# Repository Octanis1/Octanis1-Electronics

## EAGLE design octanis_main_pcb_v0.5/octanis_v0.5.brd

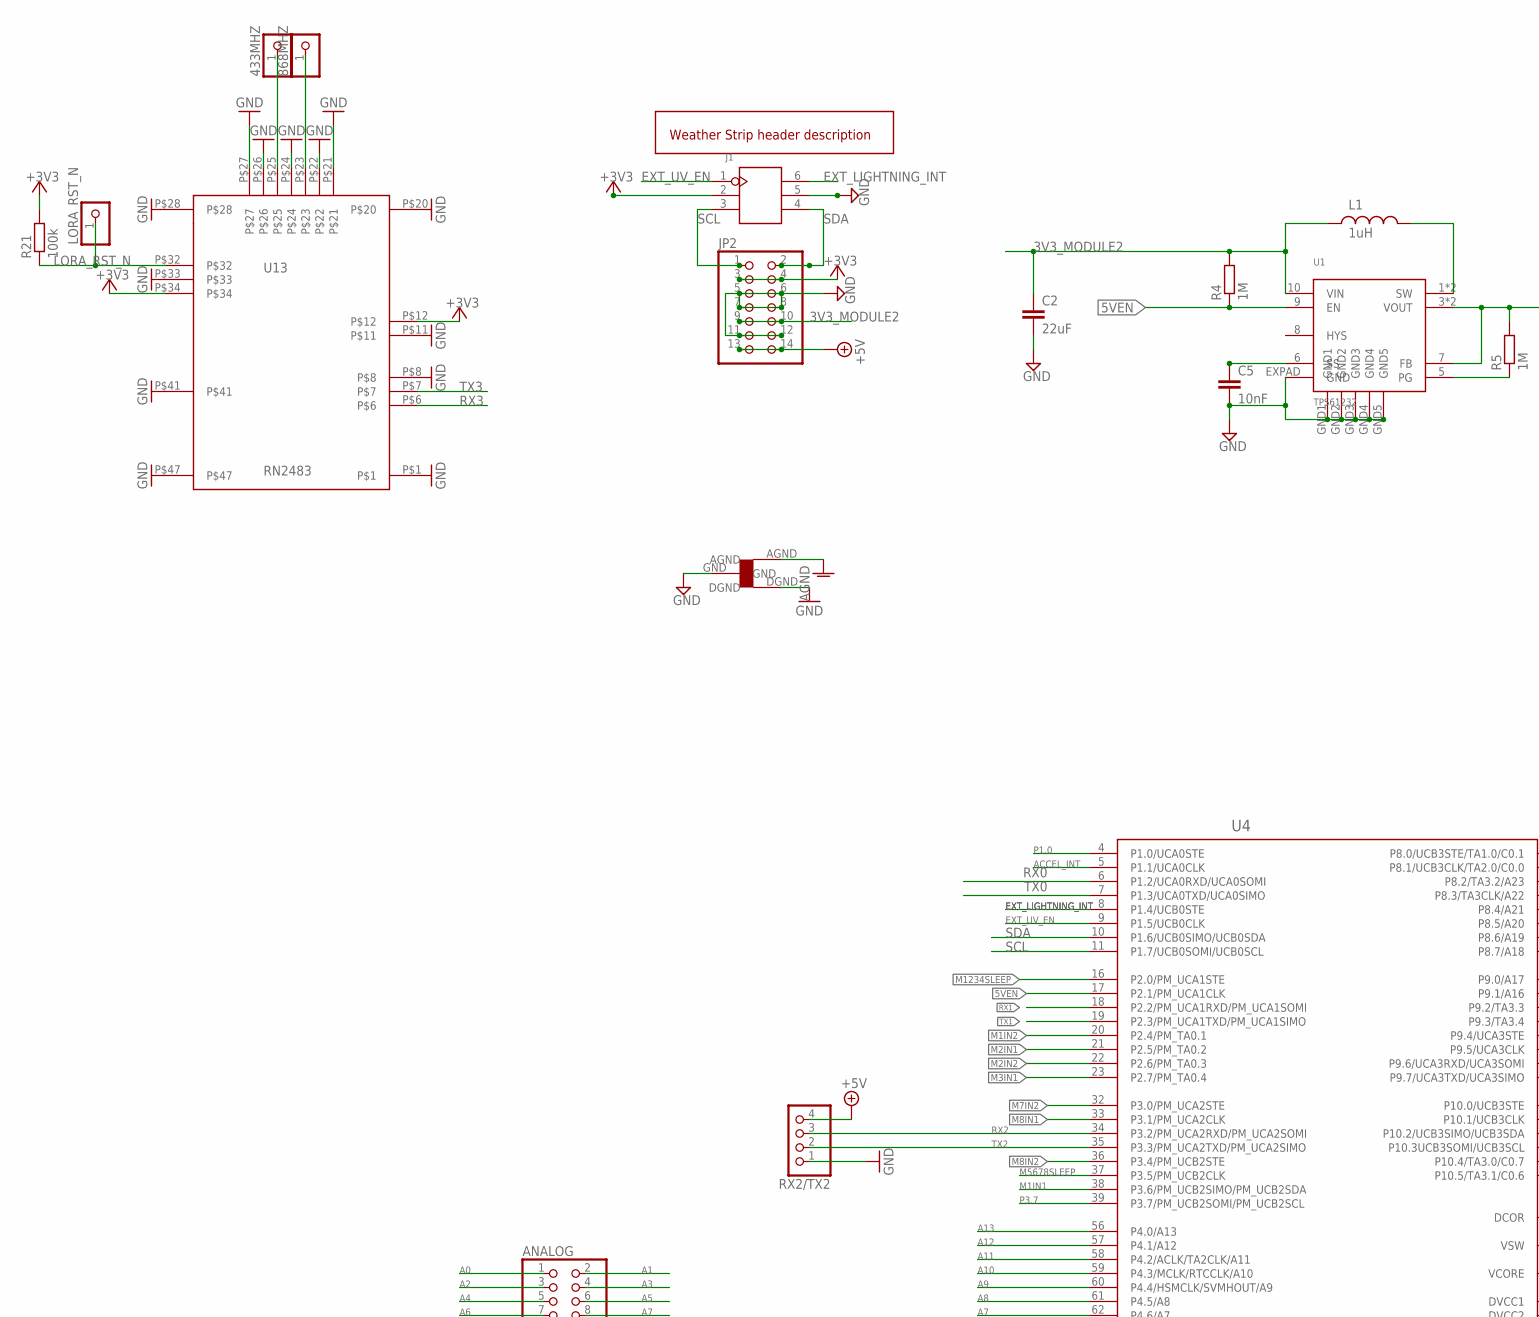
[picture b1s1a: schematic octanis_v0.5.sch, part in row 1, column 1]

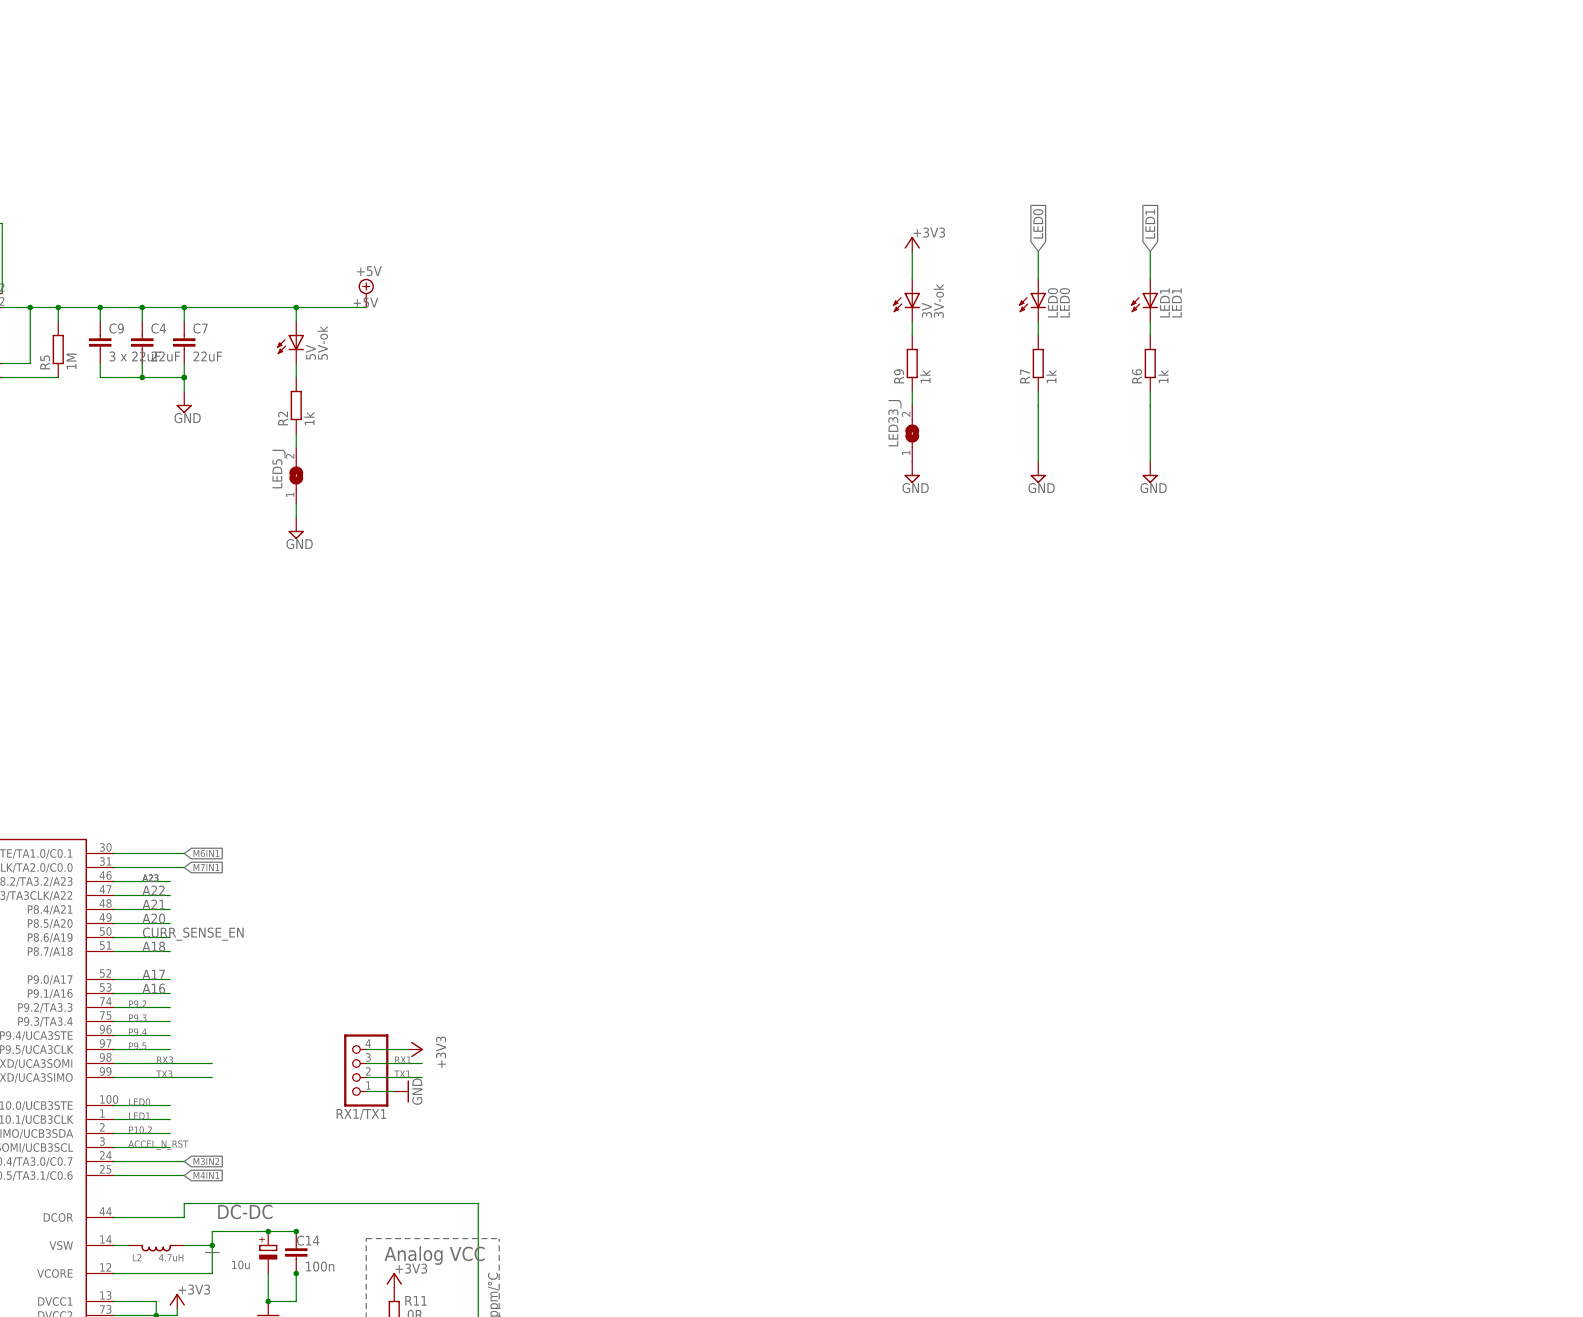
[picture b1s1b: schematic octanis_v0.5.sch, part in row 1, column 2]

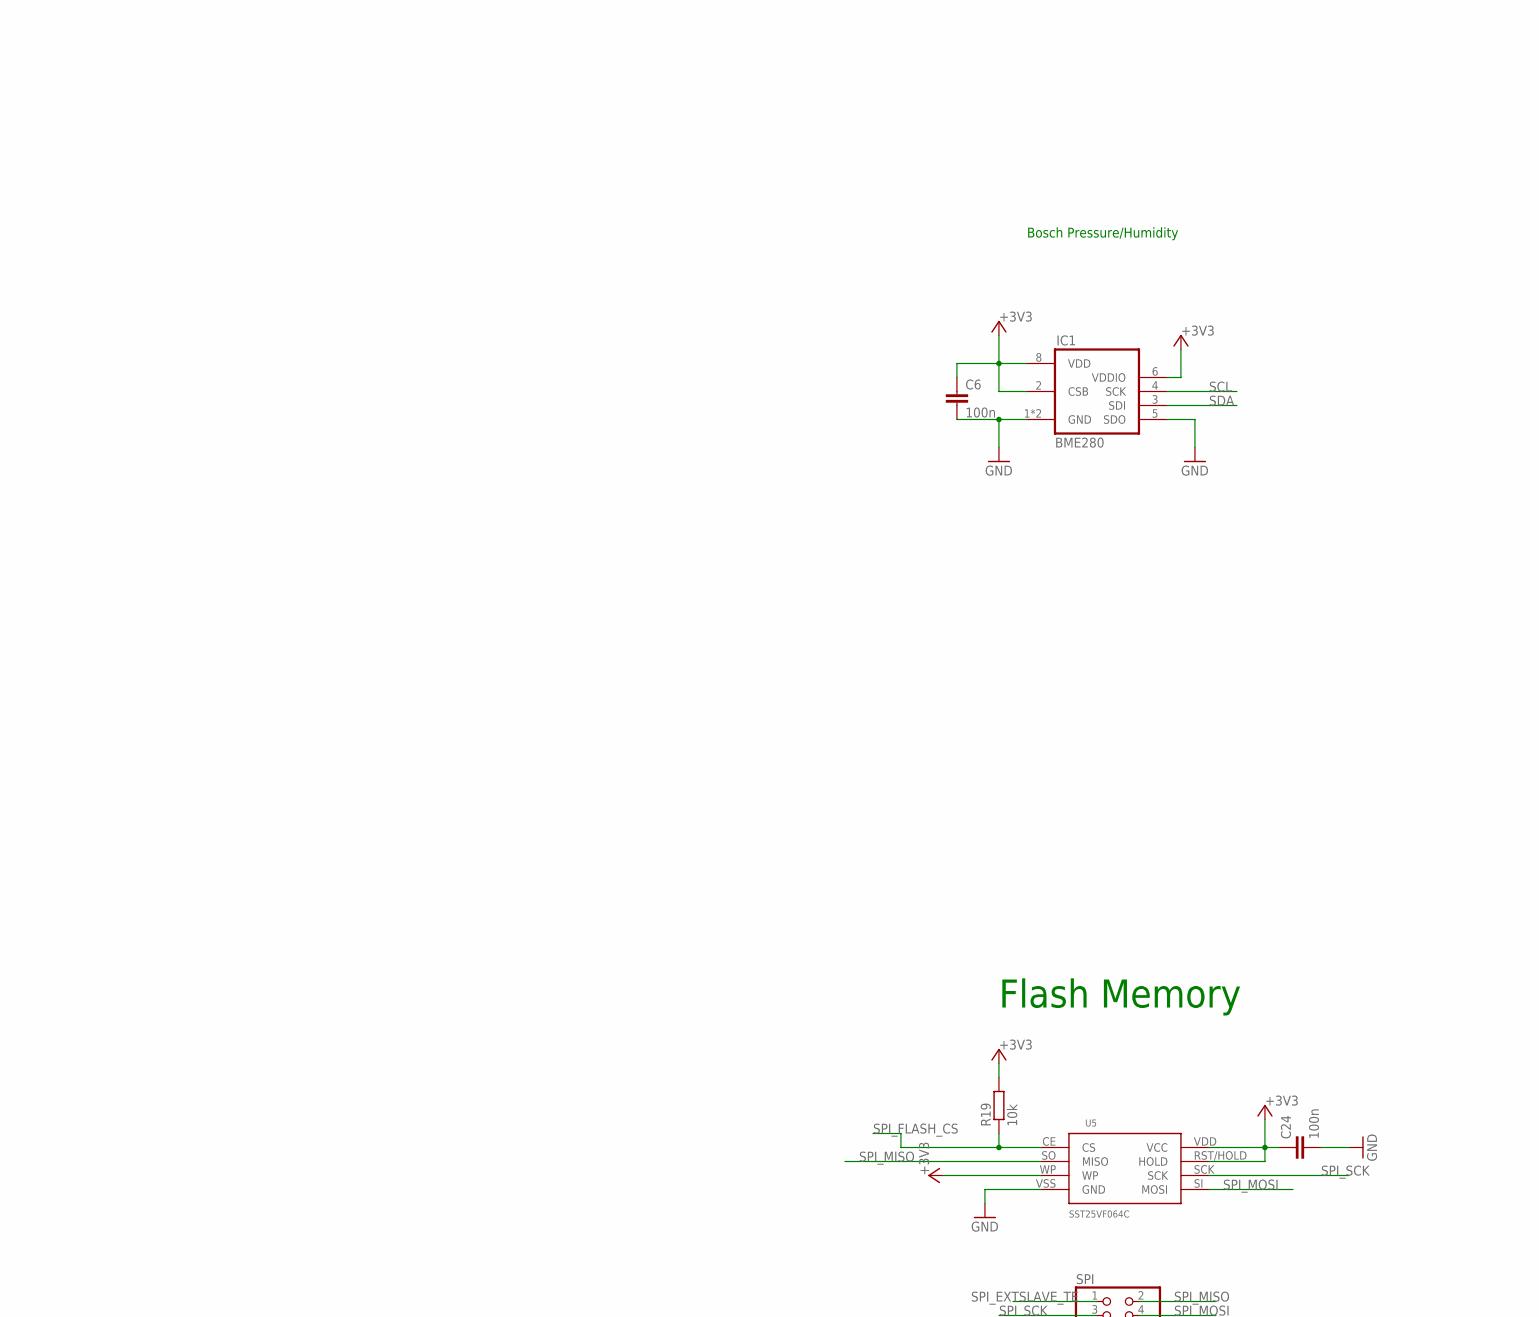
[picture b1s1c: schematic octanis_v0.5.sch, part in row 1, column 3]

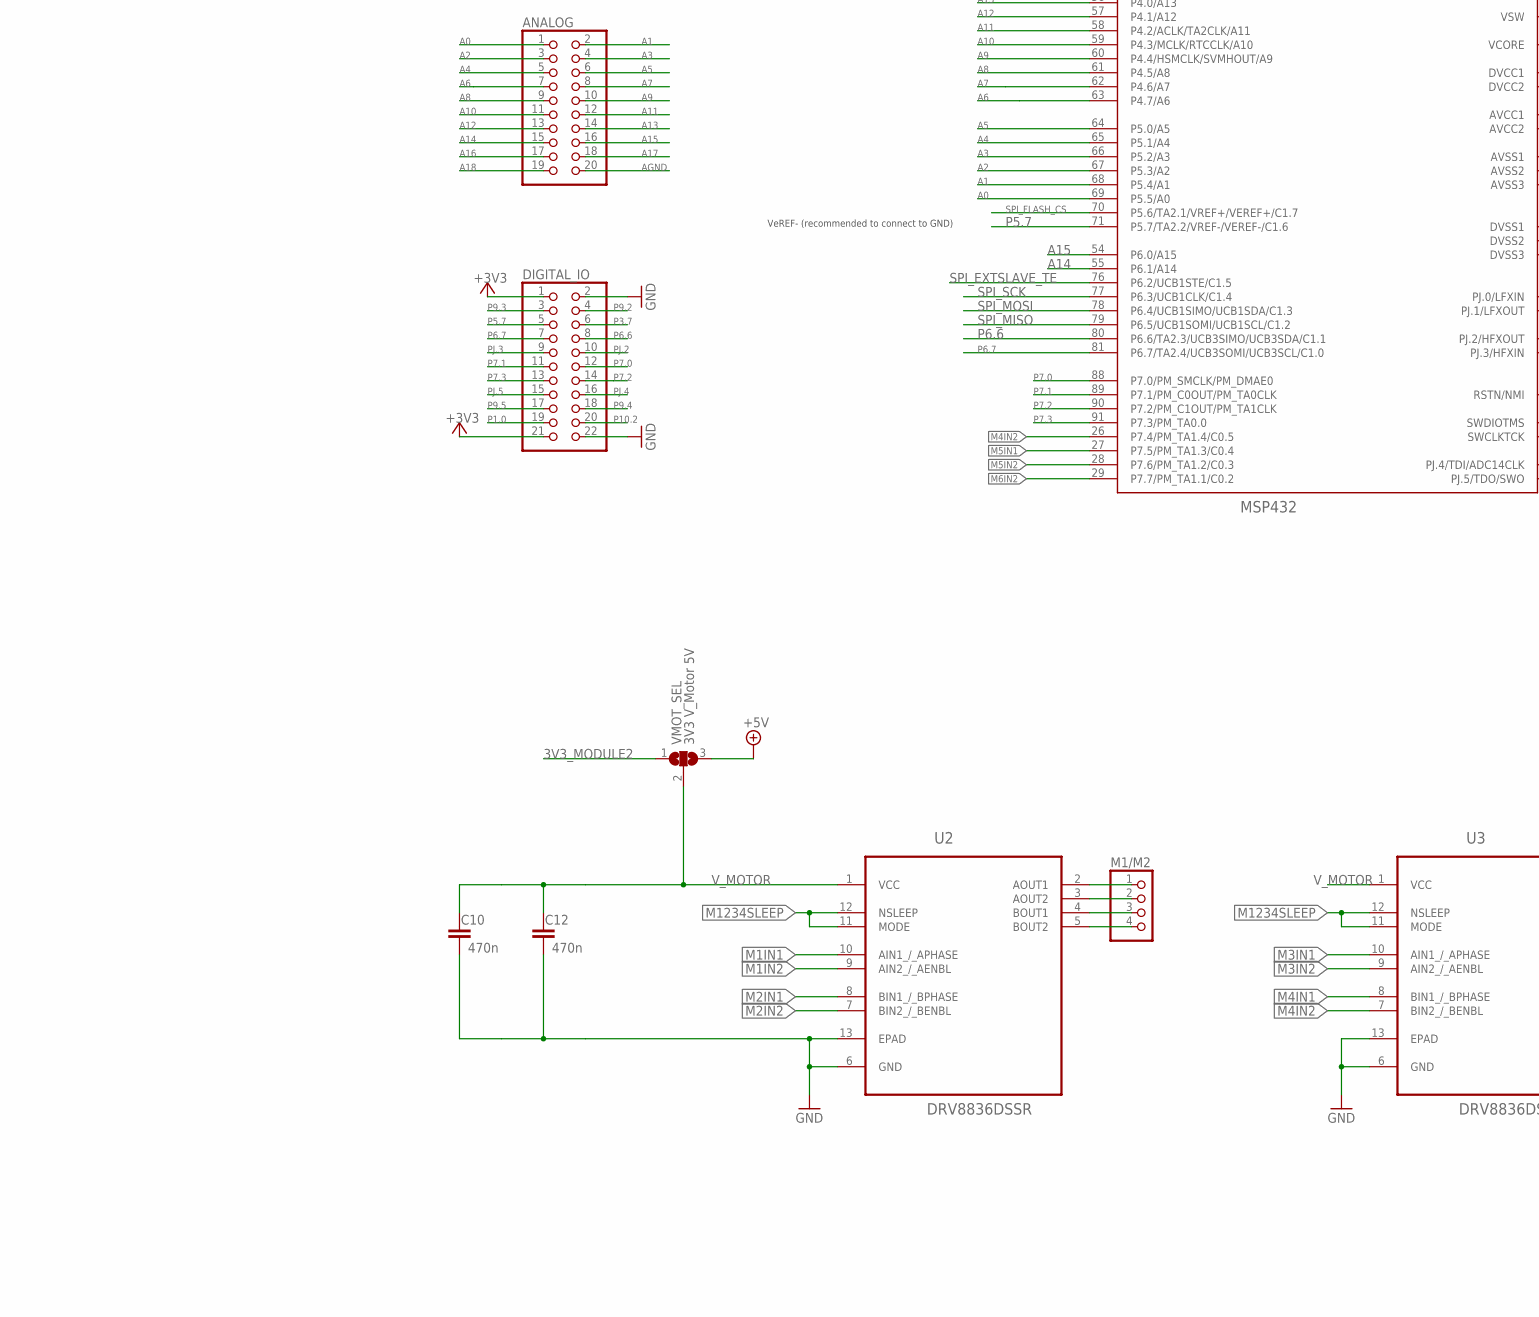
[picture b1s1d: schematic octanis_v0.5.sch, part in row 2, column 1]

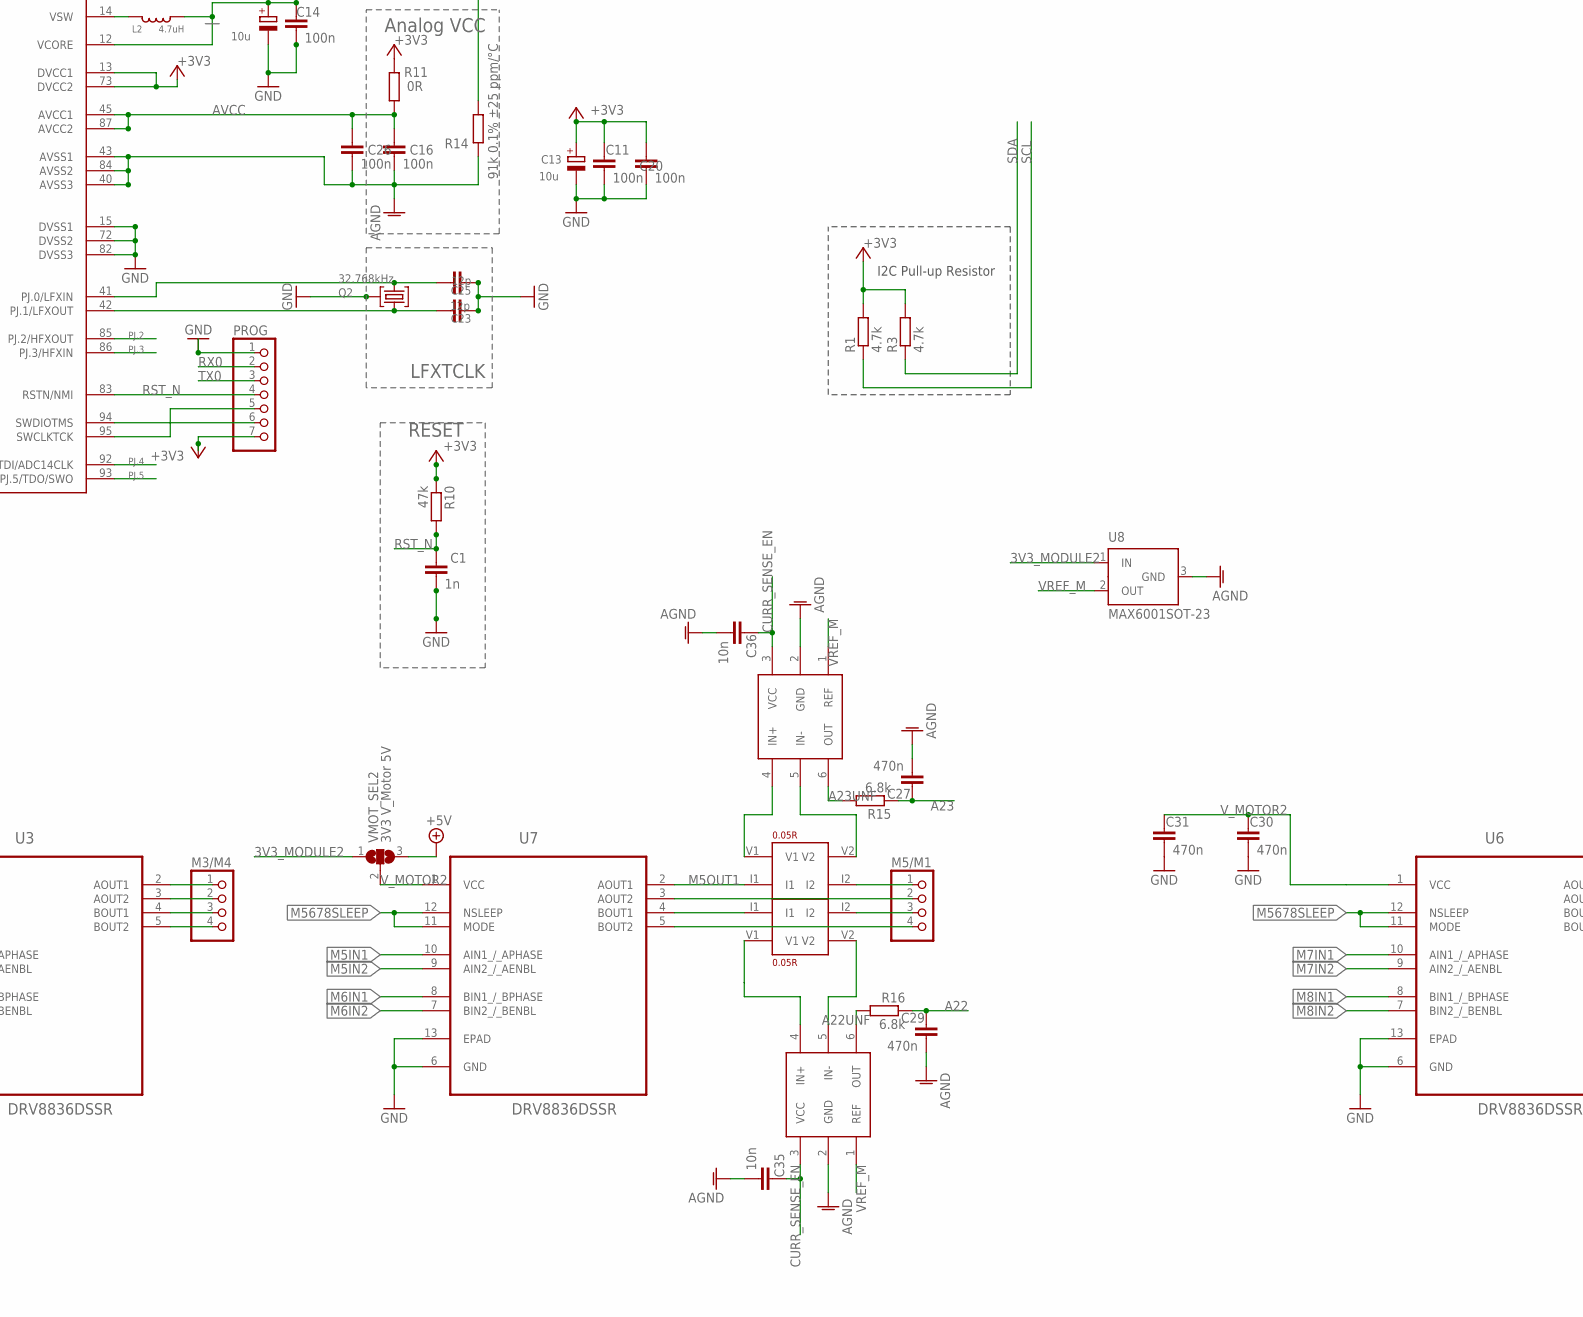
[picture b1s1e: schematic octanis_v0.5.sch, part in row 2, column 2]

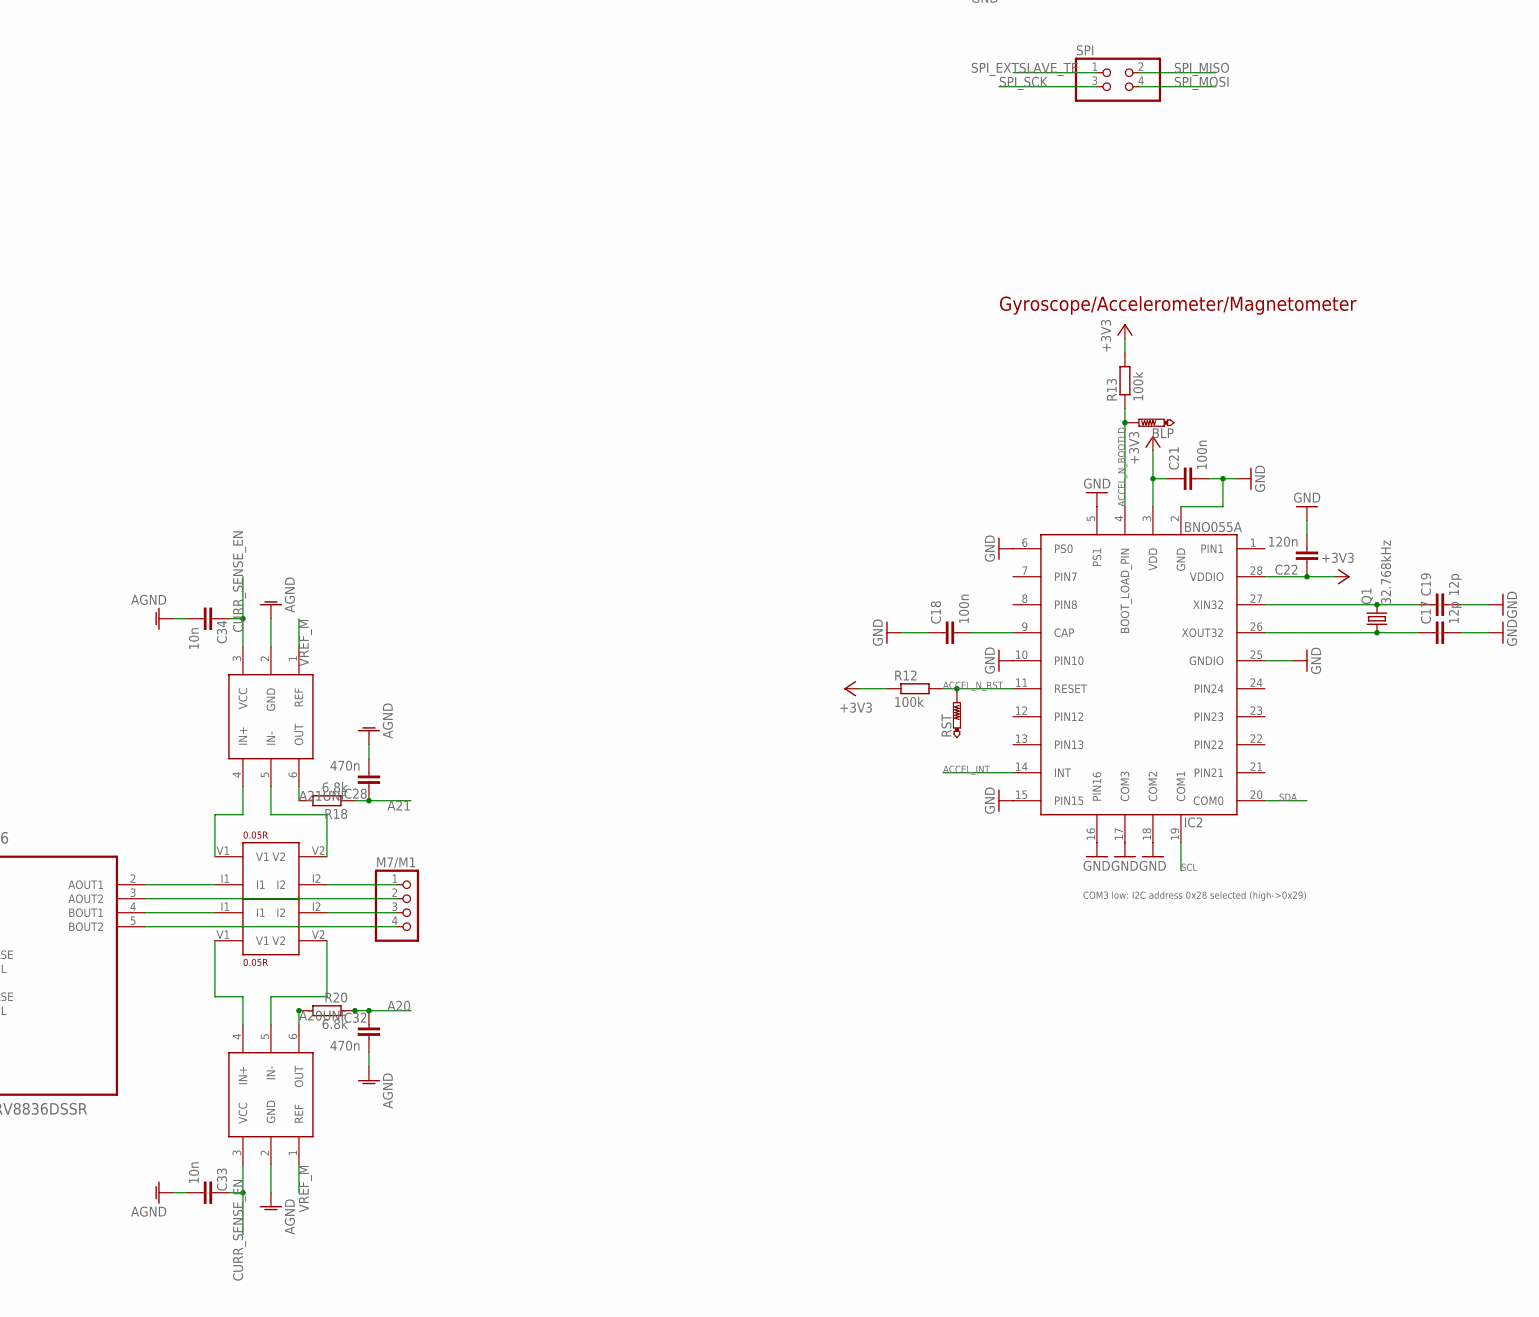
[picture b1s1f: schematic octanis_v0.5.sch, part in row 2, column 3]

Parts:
3V: 3V-ok; CHIPLED_0603
5V: 5V-ok; CHIPLED_0603
433MHZ, 868MHZ: PINHD-1X1; 1X01
ANALOG: PINHD-2X10; 2X10
BLP: PTR1B1,27; B1,27
C1: 1n; C0603
C2, C4, C7: 22uF; C0603
C5: 10nF; C0603
C6, C11, C14, C18, C20, C21, C24: 100n; C0603
C9: 3 x 22uF; C0603
C10, C12, C27, C28, C29, C30, C31, C32: 470n; C0603
C13, C15: 10u; A/3216-18R
C16, C26: 100n; C0402
C17, C19: 12p; C0603
C22: 120n; C0603
C23, C25: 12p; C0402
C33, C34, C35, C36: 10n; C0603
DIGITAL_IO: PINHD-2X11; 2X11
IC1: BME280
IC2: BNO055A; BNO055
J1: SMD-BLUE-FEMALE-HEADER-VERT(2X3P-2.54); H2X3-SMD-2.54
JP2: PINHD-2X7; 2X07
L1: 1uH; XFL4020
L2: 4.7uH; 0806
LED0: LED0; CHIPLED_0603
LED1: LED1; CHIPLED_0603
LED5_J, LED33_J: SJ
LORA_RST_N: PINHD-1X1; 1X01
M1/M2, M3/M4, M5/M1, M7/M1: PINHD-1X04_2.54-S; 1X04-S
PROG: PINHD-1X72MM_SMD; 1X7SMD
Q1: 32.768kHz; FC-12M
Q2: 32.768kHz; MS3V-T1R
R1, R3: 4.7k; R0603
R2, R6, R7, R9: 1k; R0603
R4, R5: 1M; R0603
R10: 47k; R0603
R11: 0R; R0402
R12, R13, R21: 100k; R0603
R14: 91k 0.1% ±25 ppm/°C; R0402
R15, R16, R18, R20: 6.8k; R0603
R19: 10k; R0603
RS1, RS2, RS3, RS4: 0.05R; 4PADS_RESISTOR
RST: PTR1B1,27; B1,27
RX1/TX1, RX2/TX2: PINHD-1X04_2.54-S; 1X04-S
SPI: PINHD-2X2; 2X02
U1: TPS61232; S-PVSON-N10
U2, U3, U6, U7: DRV8836DSSR; SON50P200X300X80-13N
U4: MSP432; PZ100
U5: SST25VF064C; SOIC_8-LEAD
U8: MAX6001SOT-23; MAX6001
U9, U10, U11, U12: INA210; SC70-6
U13: RN2483
U$1: WEATHER_STRIP_DOCU
U$100: STARGND; STAR
VMOT_SEL, VMOT_SEL2: 3V3 V_Motor 5V; SJ_2

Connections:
3V3_MODULE2: C2.1, JP2.9, JP2.10, L1.P$1 (1), R4.2, U1.10 (VIN), U8.1 (IN), VMOT_SEL.1, VMOT_SEL2.1
5VEN: R4.1, U1.9 (EN), U4.17 (P2.1/PM_UCA1CLK)
+3V3: 3V.A, C6.1, C11.2, C13.+, C20.2, C21.1, C22.1, C24.1, DIGITAL_IO.1, DIGITAL_IO.21, IC1.2 (CSB), IC1.6 (VDDIO), IC1.8 (VDD), IC2.3 (VDD), IC2.28 (VDDIO), J1.2, JP2.3, JP2.4, PROG.7, R1.2, R3.2, R10.1, R11.2, R12.1, R13.2, R19.2, R21.2, RX1/TX1.4, U4.13 (DVCC1), U4.73 (DVCC2), U5.RST/HOLD (HOLD), U5.VDD (VCC), U5.WP, U13.P$12, U13.P$34
+5V: 5V.A, C4.1, C7.1, C9.1, JP2.13, JP2.14, R5.2, RX2/TX2.4, U1.3 (VOUT), U1.4 (VOUT), U1.7 (FB), VMOT_SEL.3, VMOT_SEL2.3
A0: ANALOG.1, U4.69 (P5.5/A0)
A1: ANALOG.2, U4.68 (P5.4/A1)
A2: ANALOG.3, U4.67 (P5.3/A2)
A3: ANALOG.4, U4.66 (P5.2/A3)
A4: ANALOG.5, U4.65 (P5.1/A4)
A5: ANALOG.6, U4.64 (P5.0/A5)
A6: ANALOG.7, U4.63 (P4.7/A6)
A7: ANALOG.8, U4.62 (P4.6/A7)
A8: ANALOG.9, U4.61 (P4.5/A8)
A9: ANALOG.10, U4.60 (P4.4/HSMCLK/SVMHOUT/A9)
A10: ANALOG.11, U4.59 (P4.3/MCLK/RTCCLK/A10)
A11: ANALOG.12, U4.58 (P4.2/ACLK/TA2CLK/A11)
A12: ANALOG.13, U4.57 (P4.1/A12)
A13: ANALOG.14, U4.56 (P4.0/A13)
A14: ANALOG.15, U4.55 (P6.1/A14)
A15: ANALOG.16, U4.54 (P6.0/A15)
A16: ANALOG.17, U4.53 (P9.1/A16)
A17: ANALOG.18, U4.52 (P9.0/A17)
A18: ANALOG.19, U4.51 (P8.7/A18)
A20: C32.2, R20.1, U4.49 (P8.5/A20)
A20UNF: R20.2, U9.6 (OUT)
A21: C28.2, R18.1, U4.48 (P8.4/A21)
A21UNF: R18.2, U10.6 (OUT)
A22: C29.2, R16.1, U4.47 (P8.3/TA3CLK/A22)
A22UNF: R16.2, U11.6 (OUT)
A23: C27.2, R15.1, U4.46 (P8.2/TA3.2/A23)
A23UNF: R15.2, U12.6 (OUT)
ACCEL_INT: IC2.14 (INT), U4.5 (P1.1/UCA0CLK)
ACCEL_N_BOOTLD: BLP.TP, IC2.4 (BOOT_LOAD_PIN), R13.1
ACCEL_N_RST: IC2.11 (RESET), R12.2, RST.TP, U4.3 (P10.3UCB3SOMI/UCB3SCL)
AGND: ANALOG.20, C16.2, C26.2, C27.1, C28.1, C29.1, C32.1, C33.1, C34.1, C35.1, C36.1, R14.2, U4.40 (AVSS3), U4.43 (AVSS1), U4.84 (AVSS2), U8.3 (GND), U9.2 (GND), U10.2 (GND), U11.2 (GND), U12.2 (GND), U$100.AGND
ANT433: 433MHZ.1, U13.P$25
ANT868: 868MHZ.1, U13.P$23
AVCC: C16.1, C26.1, R11.1, U4.45 (AVCC1), U4.87 (AVCC2)
CURR_SENSE_EN: C33.2, C34.2, C35.2, C36.2, U4.50 (P8.6/A19), U9.3 (VCC), U10.3 (VCC), U11.3 (VCC), U12.3 (VCC)
EXT_LIGHTNING_INT: J1.6, U4.8 (P1.4/UCB0STE)
EXT_UV_EN: J1.1, U4.9 (P1.5/UCB0CLK)
GND: C1.1, C2.2, C4.2, C5.2, C6.2, C7.2, C9.2, C10.1, C11.1, C12.1, C13.-, C14.1, C15.-, C17.2, C18.1, C19.2, C20.1, C21.2, C22.2, C23.1, C24.2, C25.1, C30.1, C31.1, DIGITAL_IO.2, DIGITAL_IO.22, IC1.1 (GND), IC1.5 (SDO), IC1.7 (GND), IC2.2 (GND), IC2.5 (PS1), IC2.6 (PS0), IC2.10 (PIN10), IC2.15 (PIN15), IC2.16 (PIN16), IC2.17 (COM3), IC2.18 (COM2), IC2.25 (GNDIO), J1.5, JP2.5, JP2.6, JP2.7, JP2.8, JP2.11, JP2.12, LED5_J.1, LED33_J.1, PROG.1, Q2.P3 (GND), R6.1, R7.1, RX1/TX1.1, RX2/TX2.1, U1.EXPAD (GND), U1.GND1, U1.GND2, U1.GND3, U1.GND4, U1.GND5, U2.6 (GND), U2.13 (EPAD), U3.6 (GND), U3.13 (EPAD), U4.15 (DVSS1), U4.72 (DVSS2), U4.82 (DVSS3), U5.VSS (GND), U6.6 (GND), U6.13 (EPAD), U7.6 (GND), U7.13 (EPAD), U13.P$1, U13.P$8, U13.P$11, U13.P$20, U13.P$21, U13.P$22, U13.P$24, U13.P$26, U13.P$27, U13.P$28, U13.P$33, U13.P$41, U13.P$47, U$100.DGND, U$100.GND
IND: L1.P$2 (2), U1.1 (SW), U1.2 (SW)
LED0: LED0.A, U4.100 (P10.0/UCB3STE)
LED1: LED1.A, U4.1 (P10.1/UCB3CLK)
LORA_RST_N: LORA_RST_N.1, R21.1, U13.P$32
M1IN1: U2.10 (AIN1_/_APHASE), U4.38 (P3.6/PM_UCB2SIMO/PM_UCB2SDA)
M1IN2: U2.9 (AIN2_/_AENBL), U4.20 (P2.4/PM_TA0.1)
M2IN1: U2.8 (BIN1_/_BPHASE), U4.21 (P2.5/PM_TA0.2)
M2IN2: U2.7 (BIN2_/_BENBL), U4.22 (P2.6/PM_TA0.3)
M3IN1: U3.10 (AIN1_/_APHASE), U4.23 (P2.7/PM_TA0.4)
M3IN2: U3.9 (AIN2_/_AENBL), U4.24 (P10.4/TA3.0/C0.7)
M4IN1: U3.8 (BIN1_/_BPHASE), U4.25 (P10.5/TA3.1/C0.6)
M4IN2: U3.7 (BIN2_/_BENBL), U4.26 (P7.4/PM_TA1.4/C0.5)
M5IN1: U4.27 (P7.5/PM_TA1.3/C0.4), U7.10 (AIN1_/_APHASE)
M5IN2: U4.28 (P7.6/PM_TA1.2/C0.3), U7.9 (AIN2_/_AENBL)
M5OUT1: RS4.I1, U7.2 (AOUT1)
M6IN1: U4.30 (P8.0/UCB3STE/TA1.0/C0.1), U7.8 (BIN1_/_BPHASE)
M6IN2: U4.29 (P7.7/PM_TA1.1/C0.2), U7.7 (BIN2_/_BENBL)
M7IN1: U4.31 (P8.1/UCB3CLK/TA2.0/C0.0), U6.10 (AIN1_/_APHASE)
M7IN2: U4.32 (P3.0/PM_UCA2STE), U6.9 (AIN2_/_AENBL)
M8IN1: U4.33 (P3.1/PM_UCA2CLK), U6.8 (BIN1_/_BPHASE)
M8IN2: U4.36 (P3.4/PM_UCB2STE), U6.7 (BIN2_/_BENBL)
M1234SLEEP: U2.11 (MODE), U2.12 (NSLEEP), U3.11 (MODE), U3.12 (NSLEEP), U4.16 (P2.0/PM_UCA1STE)
M5678SLEEP: U4.37 (P3.5/PM_UCB2CLK), U6.11 (MODE), U6.12 (NSLEEP), U7.11 (MODE), U7.12 (NSLEEP)
unnamed: C14.2, C15.+, L2.1, U4.12 (VCORE)
unnamed: R5.1, U1.5 (PG)
unnamed: 3V.C, R9.2
unnamed: LED0.C, R7.2
unnamed: LED1.C, R6.2
unnamed: C23.2, Q2.P2 (2), U4.41 (PJ.0/LFXIN)
unnamed: C25.2, Q2.P1 (1), U4.42 (PJ.1/LFXOUT)
unnamed: M3/M4.1, U3.2 (AOUT1)
unnamed: LED5_J.2, R2.1
unnamed: RS4.V2, U12.5 (IN-)
unnamed: RS4.V1, U12.4 (IN+)
unnamed: C18.2, IC2.9 (CAP)
unnamed: C19.1, IC2.27 (XIN32), Q1.2
unnamed: M5/M1.1, RS4.I2
unnamed: RS3.V1, U11.4 (IN+)
unnamed: RS3.V2, U11.5 (IN-)
unnamed: RS3.I1, U7.4 (BOUT1)
unnamed: LED33_J.2, R9.1
unnamed: M5/M1.3, RS3.I2
unnamed: RS2.V2, U10.5 (IN-)
unnamed: RS2.V1, U10.4 (IN+)
unnamed: RS1.V2, U9.5 (IN-)
unnamed: RS1.V1, U9.4 (IN+)
unnamed: M7/M1.1, RS2.I2
unnamed: R14.1, U4.44 (DCOR)
unnamed: L2.2, U4.14 (VSW)
unnamed: RS1.I1, U6.4 (BOUT1)
unnamed: RS2.I1, U6.2 (AOUT1)
unnamed: M7/M1.3, RS1.I2
unnamed: M5/M1.2, U7.3 (AOUT2)
unnamed: M3/M4.2, U3.3 (AOUT2)
unnamed: M3/M4.3, U3.4 (BOUT1)
unnamed: M3/M4.4, U3.5 (BOUT2)
unnamed: C5.1, U1.6 (SS)
unnamed: M5/M1.4, U7.5 (BOUT2)
unnamed: 5V.C, R2.2
unnamed: M7/M1.4, U6.5 (BOUT2)
unnamed: M1/M2.1, U2.2 (AOUT1)
unnamed: M1/M2.2, U2.3 (AOUT2)
unnamed: M1/M2.3, U2.4 (BOUT1)
unnamed: M1/M2.4, U2.5 (BOUT2)
unnamed: M7/M1.2, U6.3 (AOUT2)
unnamed: C17.1, IC2.26 (XOUT32), Q1.1
unnamed: PROG.6, U4.94 (SWDIOTMS)
unnamed: PROG.5, U4.95 (SWCLKTCK)
P1.0: DIGITAL_IO.19, U4.4 (P1.0/UCA0STE)
P3.7: DIGITAL_IO.6, U4.39 (P3.7/PM_UCB2SOMI/PM_UCB2SCL)
P5.7: DIGITAL_IO.5, U4.71 (P5.7/TA2.2/VREF-/VEREF-/C1.6)
P6.6: DIGITAL_IO.8, U4.80 (P6.6/TA2.3/UCB3SIMO/UCB3SDA/C1.1)
P6.7: DIGITAL_IO.7, U4.81 (P6.7/TA2.4/UCB3SOMI/UCB3SCL/C1.0)
P7.0: DIGITAL_IO.12, U4.88 (P7.0/PM_SMCLK/PM_DMAE0)
P7.1: DIGITAL_IO.11, U4.89 (P7.1/PM_C0OUT/PM_TA0CLK)
P7.2: DIGITAL_IO.14, U4.90 (P7.2/PM_C1OUT/PM_TA1CLK)
P7.3: DIGITAL_IO.13, U4.91 (P7.3/PM_TA0.0)
P9.2: DIGITAL_IO.4, U4.74 (P9.2/TA3.3)
P9.3: DIGITAL_IO.3, U4.75 (P9.3/TA3.4)
P9.4: DIGITAL_IO.18, U4.96 (P9.4/UCA3STE)
P9.5: DIGITAL_IO.17, U4.97 (P9.5/UCA3CLK)
P10.2: DIGITAL_IO.20, U4.2 (P10.2/UCB3SIMO/UCB3SDA)
PJ.2: DIGITAL_IO.10, U4.85 (PJ.2/HFXOUT)
PJ.3: DIGITAL_IO.9, U4.86 (PJ.3/HFXIN)
PJ.4: DIGITAL_IO.16, U4.92 (PJ.4/TDI/ADC14CLK)
PJ.5: DIGITAL_IO.15, U4.93 (PJ.5/TDO/SWO)
RST_N: C1.2, PROG.4, R10.2, U4.83 (RSTN/NMI)
RX0: PROG.2, U4.6 (P1.2/UCA0RXD/UCA0SOMI)
RX1: RX1/TX1.3, U4.18 (P2.2/PM_UCA1RXD/PM_UCA1SOMI)
RX2: RX2/TX2.3, U4.34 (P3.2/PM_UCA2RXD/PM_UCA2SOMI)
RX3: U4.98 (P9.6/UCA3RXD/UCA3SOMI), U13.P$6
SCL: IC1.4 (SCK), IC2.19 (COM1), J1.3, JP2.1, R1.1, U4.11 (P1.7/UCB0SOMI/UCB0SCL)
SDA: IC1.3 (SDI), IC2.20 (COM0), J1.4, JP2.2, R3.1, U4.10 (P1.6/UCB0SIMO/UCB0SDA)
SPI_EXTSLAVE_TE: SPI.1, U4.76 (P6.2/UCB1STE/C1.5)
SPI_FLASH_CS: R19.1, U4.70 (P5.6/TA2.1/VREF+/VEREF+/C1.7), U5.CE (CS)
SPI_MISO: SPI.2, U4.79 (P6.5/UCB1SOMI/UCB1SCL/C1.2), U5.SO (MISO)
SPI_MOSI: SPI.4, U4.78 (P6.4/UCB1SIMO/UCB1SDA/C1.3), U5.SI (MOSI)
SPI_SCK: SPI.3, U4.77 (P6.3/UCB1CLK/C1.4), U5.SCK
TX0: PROG.3, U4.7 (P1.3/UCA0TXD/UCA0SIMO)
TX1: RX1/TX1.2, U4.19 (P2.3/PM_UCA1TXD/PM_UCA1SIMO)
TX2: RX2/TX2.2, U4.35 (P3.3/PM_UCA2TXD/PM_UCA2SIMO)
TX3: U4.99 (P9.7/UCA3TXD/UCA3SIMO), U13.P$7
VREF_M: U8.2 (OUT), U9.1 (REF), U10.1 (REF), U11.1 (REF), U12.1 (REF)
V_MOTOR: C10.2, C12.2, U2.1 (VCC), U3.1 (VCC), VMOT_SEL.2
V_MOTOR2: C30.2, C31.2, U6.1 (VCC), U7.1 (VCC), VMOT_SEL2.2

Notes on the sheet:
LFXTCLK
Analog VCC
I2C Pull-up Resistor
Flash Memory
Gyroscope/Accelerometer/Magnetometer
Bosch Pressure/Humidity
DC-DC
COM3 low: I2C address 0x28 selected (high->0x29)
VeREF- (recommended to connect to GND)
RESET

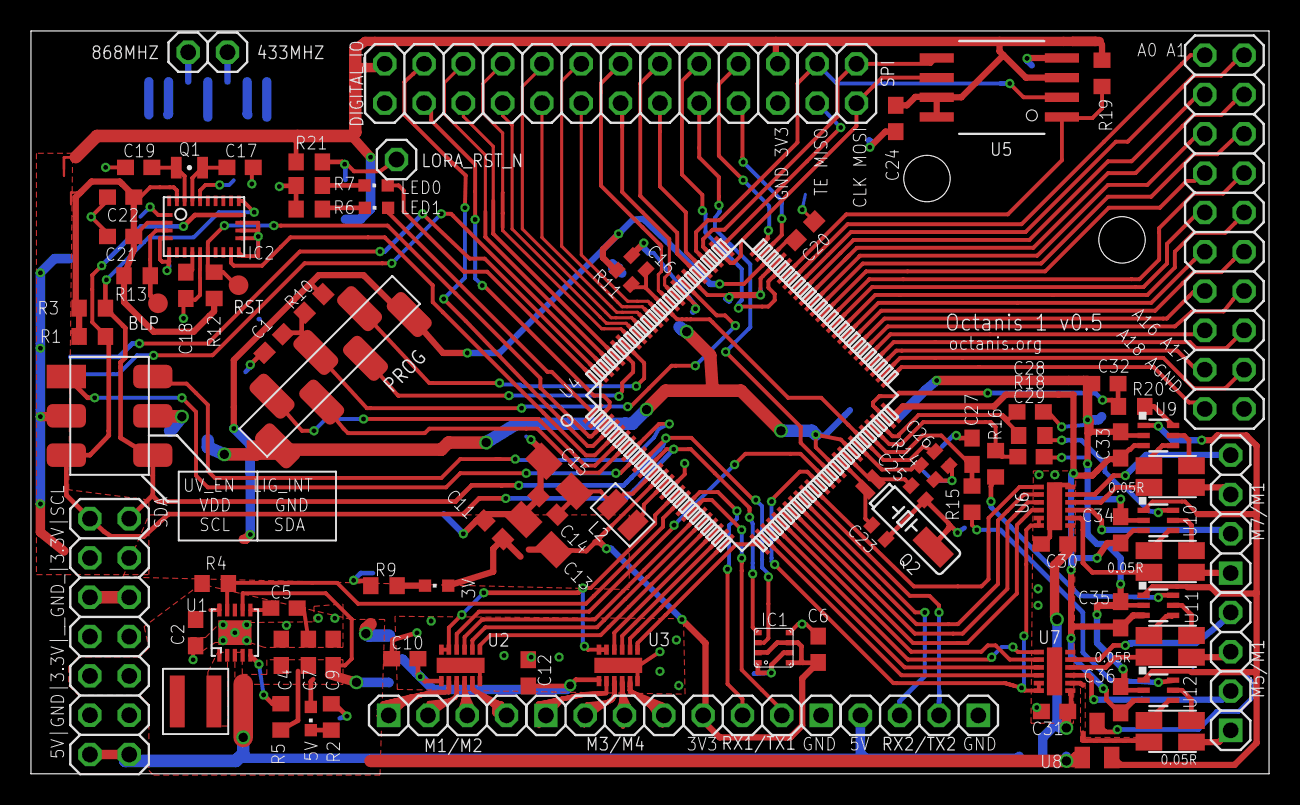
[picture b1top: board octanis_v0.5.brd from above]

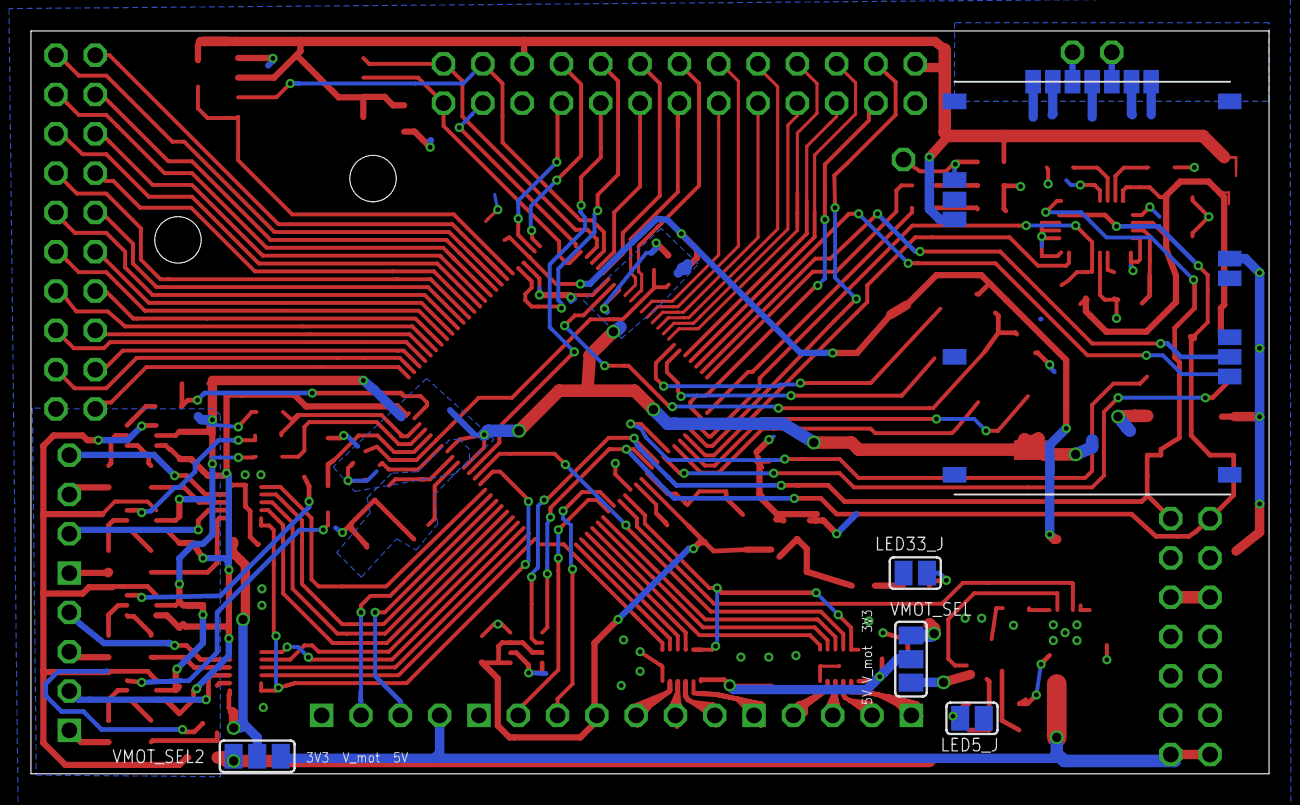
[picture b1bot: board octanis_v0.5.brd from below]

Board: 2 copper layers, 80.0 x 48.0 mm, 103 parts (5 on the bottom side), 147 nets.

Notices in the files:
parts and their libraries:
SparkFun-Aesthetics: Licensing: CC v3.0 Share-Alike You are welcome to use this library for commercial purposes.
SparkFun-Retired: Licensing:Creative Commons ShareAlike 4.0 International - https://creativecommons.org/licenses/by-sa/4.0
